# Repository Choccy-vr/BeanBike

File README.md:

# BeanBike

A DIY smart eBike display and controller.

## Why?

I made this because I really like eBikes; they are just fun. I have always wanted my own, but off the shelf they are way too expensive. So I thought of going the custom route, making my own controller. But then I thought, if I am really going to do this, I am not going to get some normal boring eBike I want my eBike. And that is how this came to be.

## Pictures!

### PCBs

#### Controller

#### Display

## BOM

|Product Name           |Product Description            |Product Link                                                                                                                                                                                                                                                                                                                                                                                                                                                                                                                                                                                                                                                                                                                                                                        |Product unit price|Product amount|Product Cost|Total (Before Tax + Shipping)|Total (Without Shipping)|Total  |
|-----------------------|-------------------------------|------------------------------------------------------------------------------------------------------------------------------------------------------------------------------------------------------------------------------------------------------------------------------------------------------------------------------------------------------------------------------------------------------------------------------------------------------------------------------------------------------------------------------------------------------------------------------------------------------------------------------------------------------------------------------------------------------------------------------------------------------------------------------------|------------------|--------------|------------|-----------------------------|------------------------|-------|
|Display-PCB            |PCB for display                |https://jlcpcb.com/                                                                                                                                                                                                                                                                                                                                                                                                                                                                                                                                                                                                                                                                                                                                                                 |4.12              |5             |$20.58      |$198.40                      |$212.29                 |$259.05|
|2x20 Socket            |Socket for Pi                  |https://www.digikey.com/en/products/detail/sullins-connector-solutions/SFH11-PBPC-D20-ST-BK/1990093                                                                                                                                                                                                                                                                                                                                                                                                                                                                                                                                                                                                                                                                                 |1.52              |1             |$1.52       |                             |                        |       |
|2x3 Header             |Expansion Pins                 |https://www.digikey.com/en/products/detail/sullins-connector-solutions/PBC03DAAN/861061                                                                                                                                                                                                                                                                                                                                                                                                                                                                                                                                                                                                                                                                                             |0.58              |2             |$1.16       |                             |                        |       |
|Display                |Display for eBike              |https://www.waveshare.com/product/displays/lcd-oled/lcd-oled-2/3.5inch-480x800-lcd.htm                                                                                                                                                                                                                                                                                                                                                                                                                                                                                                                                                                                                                                                                                              |44.99             |1             |$44.99      |                             |                        |       |
|Mini-HDMI to HDMI Cable|HDMI cable for display         |https://www.aliexpress.us/item/3256809615077123.html?spm=a2g0o.productlist.main.8.2665zmZAzmZA7N&aem_p4p_detail=202510251350533820414637980920002448901&algo_pvid=f852252a-7ad9-43c3-a8da-4e5a7b5fc53c&algo_exp_id=f852252a-7ad9-43c3-a8da-4e5a7b5fc53c-7&pdp_ext_f=%7B%22order%22%3A%22111%22%2C%22eval%22%3A%221%22%2C%22fromPage%22%3A%22search%22%7D&pdp_npi=6%40dis%21USD%214.00%210.99%21%21%214.00%210.99%21%402101d93a17614254531974823e32a0%2112000050211110398%21sea%21US%210%21ABX%211%210%21n_tag%3A-29910%3Bd%3A487c6e50%3Bm03_new_user%3A-29895%3BpisId%3A5000000187467530&curPageLogUid=s5fbXvPEQDyt&utparam-url=scene%3Asearch%7Cquery_from%3A%7Cx_object_id%3A1005009801391875%7C_p_origin_prod%3A&search_p4p_id=202510251350533820414637980920002448901_2         |1.99              |1             |$1.99       |                             |                        |       |
|Micro USB to USB C     |USB cable for display          |https://www.amazon.com/DteeDck-Adapter-Braided-Charging-Transmission/dp/B0BD36TZBK/ref=sr_1_3?crid=3JB4171DXJQSD&dib=eyJ2IjoiMSJ9.j7D2vrgbiLxGiZ8eLgHnYMRQBpcQriEWovB6tCvtnKIOLTDMlLoOxuHSk4-lcGFi6FHM3sO5ZKa8Dpr5FOVERj-xgS1iz99JzQZQLKl-xBtss3sl2CHqI4YVyfzRtf2d5FVlPNSBYPWBQrEoF8NK4ZHuYwldOKcTSCQnjOlM151Fnkp-68gktMK4j8L4pV9yZ8vR2BQQJ_acJUp5917qMGRKSj0DZvHJIeHgQgOO5zU.jbqUbGmHJq4WOtimEhEP5bUgwDAqksgkR2hxvEs_soo&dib_tag=se&keywords=micro%2Busb%2Bto%2Busb%2Bc&qid=1761426126&sprefix=micro%2Busb%2Bto%2Busb%2Caps%2C197&sr=8-3&th=1                                                                                                                                                                                                                                      |5.49              |1             |$5.49       |                             |                        |       |
|Controller-PCB         |PCB for controller             |https://jlcpcb.com/                                                                                                                                                                                                                                                                                                                                                                                                                                                                                                                                                                                                                                                                                                                                                                 |11.77             |5             |$58.87      |                             |                        |       |
|                       |                               |                                                                                                                                                                                                                                                                                                                                                                                                                                                                                                                                                                                                                                                                                                                                                                                    |                  |              |            |                             |                        |       |
|CSS2H-2512R-1L00F      |Shunt Resistors                |https://www.digikey.com/en/products/detail/bourns-inc/CSS2H-2512R-1L00F/6023764                                                                                                                                                                                                                                                                                                                                                                                                                                                                                                                                                                                                                                                                                                     |1.27              |3             |$3.81       |                             |                        |       |
|                       |                               |                                                                                                                                                                                                                                                                                                                                                                                                                                                                                                                                                                                                                                                                                                                                                                                    |                  |              |            |                             |                        |       |
|PAS sensor             |Pas Sensor                     |https://www.aliexpress.us/item/3256808182150916.html?spm=a2g0o.cart.0.0.15007a9db9tmpl&mp=1&pdp_npi=5%40dis%21USD%21USD%204.99%21USD%201.99%21%21USD%201.99%21%21%21%402103128817614453809426246ef042%2112000044743553170%21ct%21US%213108417632%21%211%210&_gl=1*1ddvozz*_gcl_au*MTU0MTkyODcyNS4xNzYwMTQ1Mzcx*_ga*MjA2ODc0MDM2Ni4xNzYxNDQ1Mzgy*_ga_VED1YSGNC7*czE3NjE0NDUzODIkbzEkZzAkdDE3NjE0NDUzODIkajYwJGwwJGgw&gatewayAdapt=glo2usa                                                                                                                                                                                                                                                                                                                                            |1.99              |1             |$1.99       |                             |                        |       |
|Throttle sensor        |Twist Throttle Handle          |https://www.aliexpress.us/item/3256806514034716.html?spm=a2g0o.cart.0.0.c69c38da9vOmau&mp=1&pdp_npi=5%40dis%21USD%21USD%204.63%21USD%201.99%21%21USD%201.99%21%21%21%40210337c117627140379221353e809b%2112000038044279289%21ct%21US%213108417632%21%211%210&_gl=1*1l540z1*_gcl_au*MTU0MTkyODcyNS4xNzYwMTQ1Mzcx*_ga*MjA2ODc0MDM2Ni4xNzYxNDQ1Mzgy*_ga_VED1YSGNC7*czE3NjI3MTQwMzEkbzMkZzEkdDE3NjI3MTQwMzkkajUyJGwwJGgw&gatewayAdapt=glo2usa                                                                                                                                                                                                                                                                                                                                            |1.99              |1             |$1.99       |                             |                        |       |
|Brake sensor           |Brake/shut off sensor          |https://www.aliexpress.us/item/3256805985764030.html?spm=a2g0o.cart.0.0.c69c38da9vOmau&mp=1&pdp_npi=5%40dis%21USD%21USD%2011.66%21USD%202.90%21%21USD%202.90%21%21%21%40210337c117627140379221353e809b%2112000036110573258%21ct%21US%213108417632%21%211%210&_gl=1*1sw3duy*_gcl_au*MTU0MTkyODcyNS4xNzYwMTQ1Mzcx*_ga*MjA2ODc0MDM2Ni4xNzYxNDQ1Mzgy*_ga_VED1YSGNC7*czE3NjI3MTQwMzEkbzMkZzEkdDE3NjI3MTQwNDgkajQzJGwwJGgw&gatewayAdapt=glo2usa                                                                                                                                                                                                                                                                                                                                           |5.9               |1             |$5.90       |                             |                        |       |
|MOSFET Heatsinks       |Heatsink for MOSFETs           |https://www.aliexpress.us/item/3256803892794950.html?spm=a2g0o.productlist.main.1.13c62810kwHGNA&algo_pvid=aa161256-cc13-4f43-9ac4-79cdfe83af14&algo_exp_id=aa161256-cc13-4f43-9ac4-79cdfe83af14-0&pdp_ext_f=%7B%22order%22%3A%222400%22%2C%22eval%22%3A%221%22%2C%22fromPage%22%3A%22search%22%7D&pdp_npi=6%40dis%21USD%212.12%211.99%21%21%2115.01%2114.09%21%402101d83f17614455184686341ee64b%2112000030401636260%21sea%21US%213108417632%21X%211%210%21n_tag%3A-29919%3Bd%3A487c6e50%3Bm03_new_user%3A-29895%3BpisId%3A5000000190801969&curPageLogUid=eevL79xpdQiV&utparam-url=scene%3Asearch%7Cquery_from%3A%7Cx_object_id%3A1005004079109702%7C_p_origin_prod%3A                                                                                                              |0.2               |10            |$1.99       |                             |                        |       |
|M8 Connector 2P        |Connector for brake sensor     |https://www.aliexpress.us/item/3256805115817349.html?spm=a2g0o.cart.0.0.765938daCeJANz&mp=1&pdp_npi=5%40dis%21USD%21USD%202.97%21USD%202.97%21%21USD%202.94%21%21%21%402101f11417614462386586215ea526%2112000032551815683%21ct%21US%213108417632%21%211%210&_gl=1*j0wktf*_gcl_au*MTU0MTkyODcyNS4xNzYwMTQ1Mzcx*_ga*MjA2ODc0MDM2Ni4xNzYxNDQ1Mzgy*_ga_VED1YSGNC7*czE3NjE0NDUzODIkbzEkZzEkdDE3NjE0NDYyNDAkajMkbDAkaDA.&gatewayAdapt=glo2usa                                                                                                                                                                                                                                                                                                                                             |2.97              |1             |$2.97       |                             |                        |       |
|M8 Connectors 3P       |Connectors for PAS and Throttle|https://www.aliexpress.us/item/3256805115817349.html?spm=a2g0o.cart.0.0.765938daCeJANz&mp=1&pdp_npi=5%40dis%21USD%21USD%206.99%21USD%206.99%21%21USD%206.92%21%21%21%402101f11417614462386586215ea526%2112000032551815696%21ct%21US%213108417632%21%211%210&_gl=1*j0wktf*_gcl_au*MTU0MTkyODcyNS4xNzYwMTQ1Mzcx*_ga*MjA2ODc0MDM2Ni4xNzYxNDQ1Mzgy*_ga_VED1YSGNC7*czE3NjE0NDUzODIkbzEkZzEkdDE3NjE0NDYyNDAkajMkbDAkaDA.&gatewayAdapt=glo2usa                                                                                                                                                                                                                                                                                                                                             |1.75              |4             |$6.99       |                             |                        |       |
|M8 Connector 6P        |Connector for Display          |https://www.aliexpress.us/item/3256805115817349.html?spm=a2g0o.cart.0.0.765938daCeJANz&mp=1&pdp_npi=5%40dis%21USD%21USD%203.46%21USD%203.46%21%21USD%203.43%21%21%21%402101f11417614462386586215ea526%2112000038599641962%21ct%21US%213108417632%21%211%210&_gl=1*1hyuy1y*_gcl_au*MTU0MTkyODcyNS4xNzYwMTQ1Mzcx*_ga*MjA2ODc0MDM2Ni4xNzYxNDQ1Mzgy*_ga_VED1YSGNC7*czE3NjE0NDUzODIkbzEkZzEkdDE3NjE0NDYyNDMkajYwJGwwJGgw&gatewayAdapt=glo2usa                                                                                                                                                                                                                                                                                                                                            |3.46              |1             |$2.97       |                             |                        |       |
|MOSFETs                |MOSFETs                        |https://www.digikey.com/en/products/detail/infineon-technologies/IRFB4110PBFXKMA1/22157630                                                                                                                                                                                                                                                                                                                                                                                                                                                                                                                                                                                                                                                                                          |3.06              |6             |$18.36      |                             |                        |       |
|Capacitor 680uF        |big cap for controller         |https://www.digikey.com/en/products/detail/chemi-con/EKZN630ELL681MK30S/4843904                                                                                                                                                                                                                                                                                                                                                                                                                                                                                                                                                                                                                                                                                                     |1.53              |1             |$1.53       |                             |                        |       |
|Capacitor 330uF        |big cap for controller         |https://www.digikey.com/en/products/detail/rubycon/25ZLJ330M8X11-5/3134207                                                                                                                                                                                                                                                                                                                                                                                                                                                                                                                                                                                                                                                                                                          |0.54              |1             |$0.54       |                             |                        |       |
|Screw Terminal         |Phase Connector                |https://www.digikey.com/en/products/detail/keystone-electronics/8196/316832                                                                                                                                                                                                                                                                                                                                                                                                                                                                                                                                                                                                                                                                                                         |1.24              |3             |$3.72       |                             |                        |       |
|Ring Connector         |Phase Wire connector           |https://www.digikey.com/en/products/detail/molex/0191930245/1952714                                                                                                                                                                                                                                                                                                                                                                                                                                                                                                                                                                                                                                                                                                                 |0.53              |3             |$1.59       |                             |                        |       |
|GPS module             |GPS module                     |https://www.aliexpress.us/item/3256806636967867.html?spm=a2g0o.productlist.main.8.5f294519Xppi6X&aem_p4p_detail=202511091049282176669761148710002202146&algo_pvid=408d6edc-35f6-4694-a5b1-e4b75c03ea1d&algo_exp_id=408d6edc-35f6-4694-a5b1-e4b75c03ea1d-7&pdp_ext_f=%7B%22order%22%3A%22161%22%2C%22eval%22%3A%221%22%2C%22fromPage%22%3A%22search%22%7D&pdp_npi=6%40dis%21USD%215.18%212.18%21%21%2136.69%2115.43%21%402101dedf17627141680806432e8079%2112000038417528859%21sea%21US%213108417632%21X%211%210%21n_tag%3A-29919%3Bd%3A487c6e50%3Bm03_new_user%3A-29895%3BpisId%3A5000000191724427&curPageLogUid=PXVcwqFInPA3&utparam-url=scene%3Asearch%7Cquery_from%3A%7Cx_object_id%3A1005006823282619%7C_p_origin_prod%3A&search_p4p_id=202511091049282176669761148710002202146_2|6.39              |1             |$6.39       |                             |                        |       |
|M8 Connector 5P        |Connector for ENCODER          |https://www.aliexpress.us/item/3256805115817349.html?spm=a2g0o.cart.0.0.765938daCeJANz&mp=1&pdp_npi=5%40dis%21USD%21USD%203.46%21USD%203.46%21%21USD%203.43%21%21%21%402101f11417614462386586215ea526%2112000038599641962%21ct%21US%213108417632%21%211%210&_gl=1*1hyuy1y*_gcl_au*MTU0MTkyODcyNS4xNzYwMTQ1Mzcx*_ga*MjA2ODc0MDM2Ni4xNzYxNDQ1Mzgy*_ga_VED1YSGNC7*czE3NjE0NDUzODIkbzEkZzEkdDE3NjE0NDYyNDMkajYwJGwwJGgw&gatewayAdapt=glo2usa                                                                                                                                                                                                                                                                                                                                            |3.06              |1             |$3.06       |                             |                        |       |

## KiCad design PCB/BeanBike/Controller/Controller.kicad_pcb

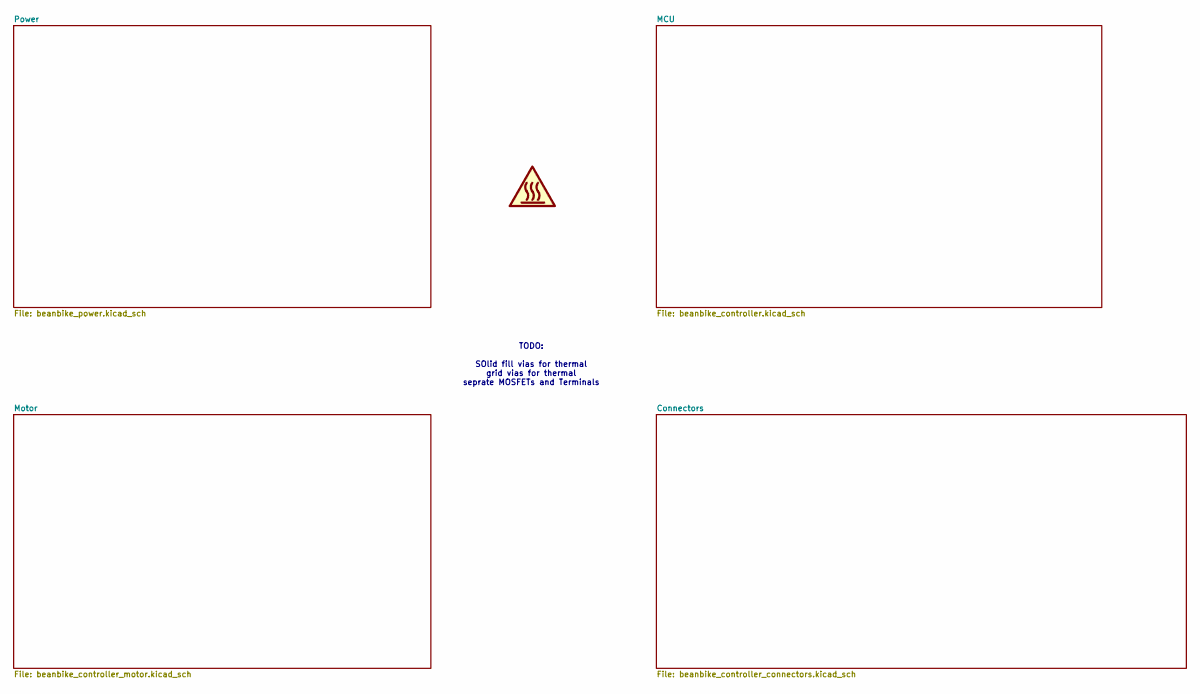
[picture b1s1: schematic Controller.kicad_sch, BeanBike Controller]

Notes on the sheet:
TODO: SOlid fill vias for thermal grid vias for thermal seprate MOSFETs and Terminals

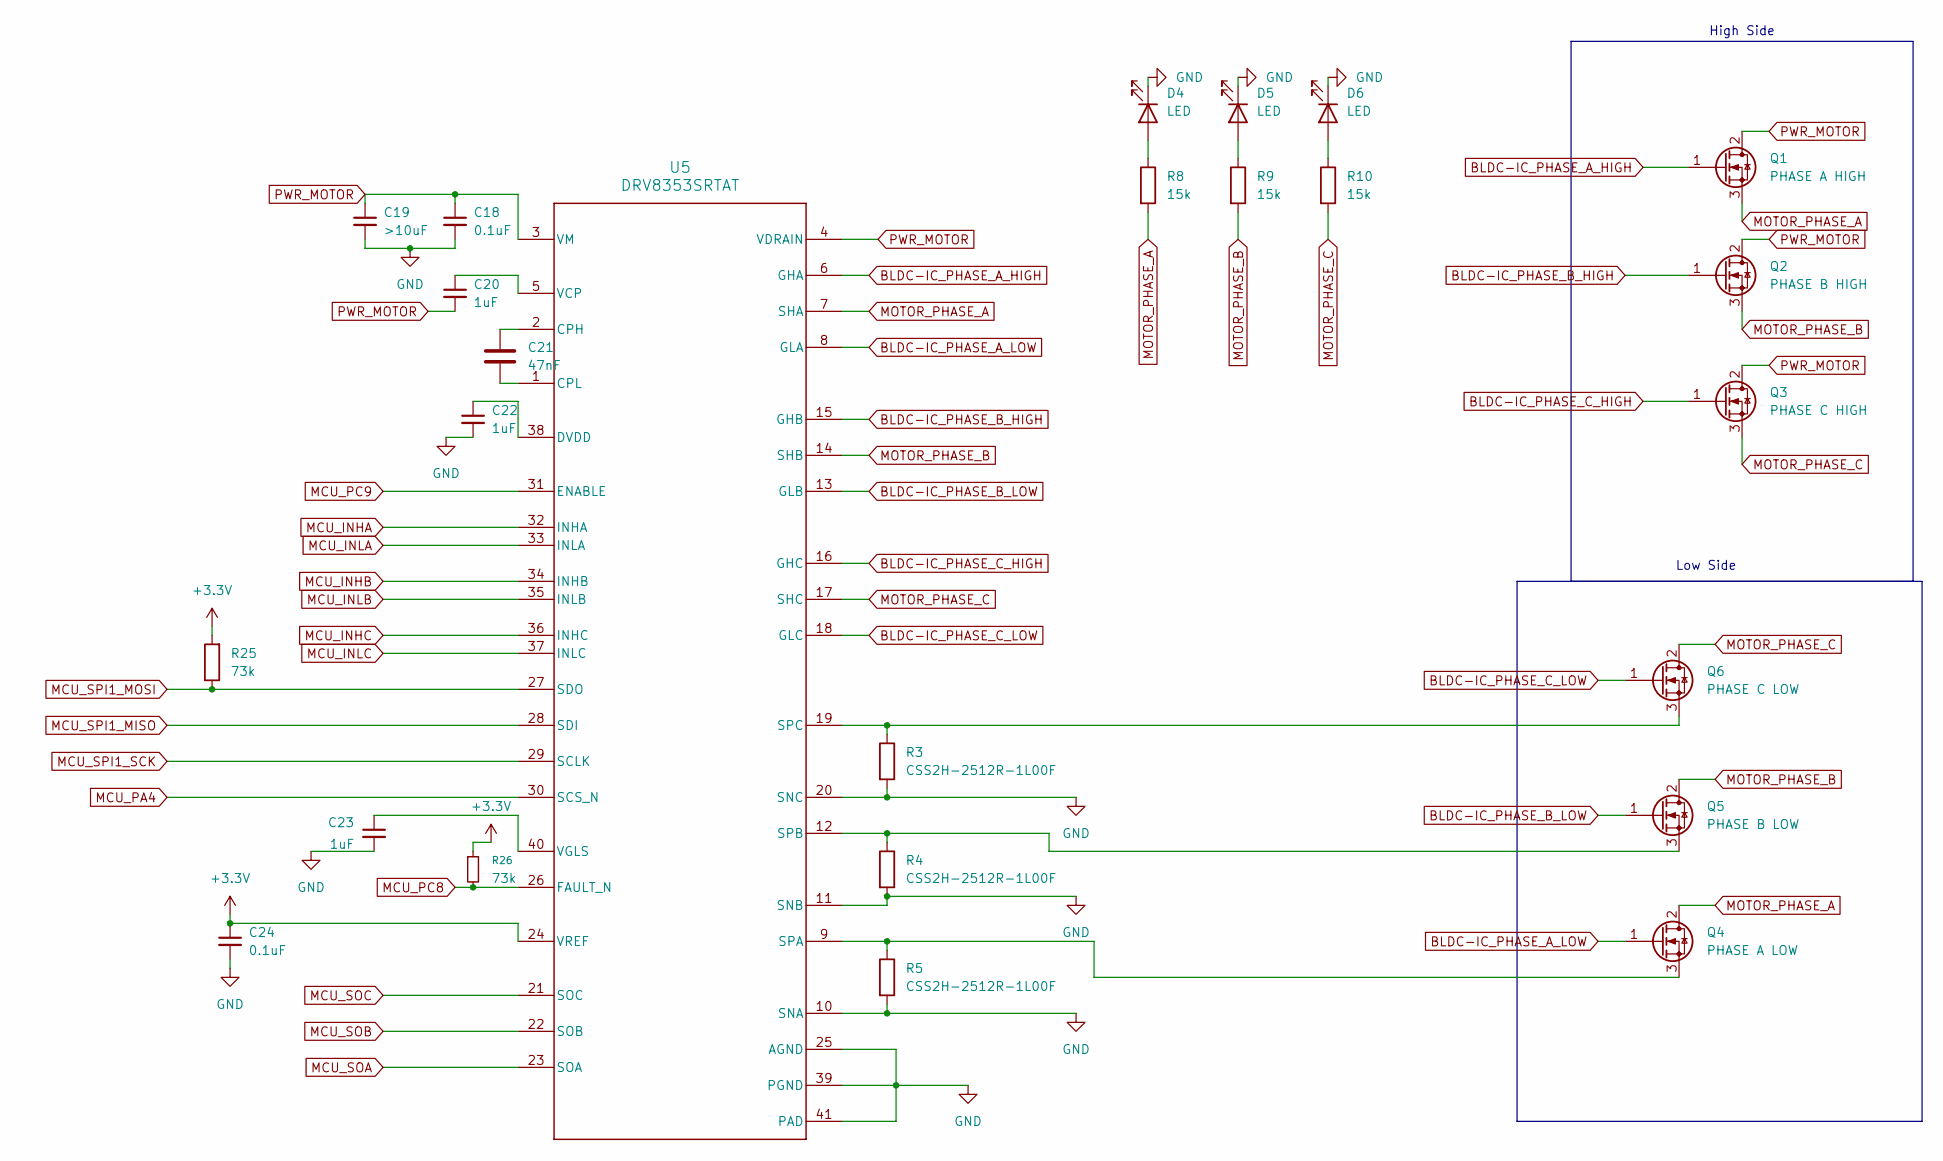
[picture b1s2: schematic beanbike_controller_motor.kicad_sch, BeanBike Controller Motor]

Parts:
C18, C24: 0.1uF; C_0402_1005Metric; LCSC C1525
C19: >10uF; C_0805_2012Metric; LCSC C45783
C20, C22, C23: 1uF; C_0402_1005Metric; LCSC C52923
C21: 47nF; C_0603_1608Metric; LCSC C1622
D4, D5, D6: LED; LED_0603_1608Metric; LCSC C2286
Q1: PHASE A HIGH; TO254P1050X476X2020-3
Q2: PHASE B HIGH; TO254P1050X476X2020-3
Q3: PHASE C HIGH; TO254P1050X476X2020-3
Q4: PHASE A LOW; TO254P1050X476X2020-3
Q5: PHASE B LOW; TO254P1050X476X2020-3
Q6: PHASE C LOW; TO254P1050X476X2020-3
R3, R4, R5: CSS2H-2512R-1L00F; RES_1L00x_BRN; LCSC C4175647
R8, R9, R10: 15k; R_0805_2012Metric; LCSC C17475
R25, R26: 73k; R_0805_2012Metric; LCSC C17819
U5: DRV8353SRTAT; QFN50P600X600X80-41N; LCSC C2150480

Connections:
+3.3V: C24.1, R25.2, R26.1, U5.24 (VREF); also elsewhere on the board
BLDC-IC_PHASE_A_HIGH: Q1.1 (G), U5.6 (GHA)
BLDC-IC_PHASE_A_LOW: Q4.1 (G), U5.8 (GLA)
BLDC-IC_PHASE_B_HIGH: Q2.1 (G), U5.15 (GHB)
BLDC-IC_PHASE_B_LOW: Q5.1 (G), U5.13 (GLB)
BLDC-IC_PHASE_C_HIGH: Q3.1 (G), U5.16 (GHC)
BLDC-IC_PHASE_C_LOW: Q6.1 (G), U5.18 (GLC)
BRAKE_GND: C18.2, C19.2, C22.2, C23.2, C24.2, D4.1 (K), D5.1 (K), D6.1 (K), R3.2, R4.2, R5.2, U5.10 (SNA), U5.11 (SNB), U5.20 (SNC), U5.25 (AGND), U5.39 (PGND), U5.41 (PAD); also elsewhere on the board
MCU_INHA: U5.32 (INHA); also elsewhere on the board
MCU_INHB: U5.34 (INHB); also elsewhere on the board
MCU_INHC: U5.36 (INHC); also elsewhere on the board
MCU_INLA: U5.33 (INLA); also elsewhere on the board
MCU_INLB: U5.35 (INLB); also elsewhere on the board
MCU_INLC: U5.37 (INLC); also elsewhere on the board
MCU_PA4: U5.30 (SCS_N); also elsewhere on the board
MCU_PC8: R26.2, U5.26 (FAULT_N); also elsewhere on the board
MCU_PC9: U5.31 (ENABLE); also elsewhere on the board
MCU_SOA: U5.23 (SOA); also elsewhere on the board
MCU_SOB: U5.22 (SOB); also elsewhere on the board
MCU_SOC: U5.21 (SOC); also elsewhere on the board
MCU_SPI1_MISO: U5.28 (SDI); also elsewhere on the board
MCU_SPI1_MOSI: R25.1, U5.27 (SDO); also elsewhere on the board
MCU_SPI1_SCK: U5.29 (SCLK); also elsewhere on the board
MOTOR_PHASE_A: Q1.3 (S), Q4.2 (D), R8.2, U5.7 (SHA); also elsewhere on the board
MOTOR_PHASE_B: Q2.3 (S), Q5.2 (D), R9.2, U5.14 (SHB); also elsewhere on the board
MOTOR_PHASE_C: Q3.3 (S), Q6.2 (D), R10.2, U5.17 (SHC); also elsewhere on the board
unnamed: D4.2 (A), R8.1
unnamed: D5.2 (A), R9.1
unnamed: D6.2 (A), R10.1
unnamed: Q4.3 (S), R5.1, U5.9 (SPA)
unnamed: Q5.3 (S), R4.1, U5.12 (SPB)
unnamed: Q6.3 (S), R3.1, U5.19 (SPC)
unnamed: C21.1, U5.2 (CPH)
unnamed: C21.2, U5.1 (CPL)
unnamed: C22.1, U5.38 (DVDD)
unnamed: C20.1, U5.5 (VCP)
unnamed: C23.1, U5.40 (VGLS)
PWR_MOTOR: C18.1, C19.1, C20.2, Q1.2 (D), Q2.2 (D), Q3.2 (D), U5.3 (VM), U5.4 (VDRAIN); also elsewhere on the board

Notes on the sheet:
High Side
Low Side

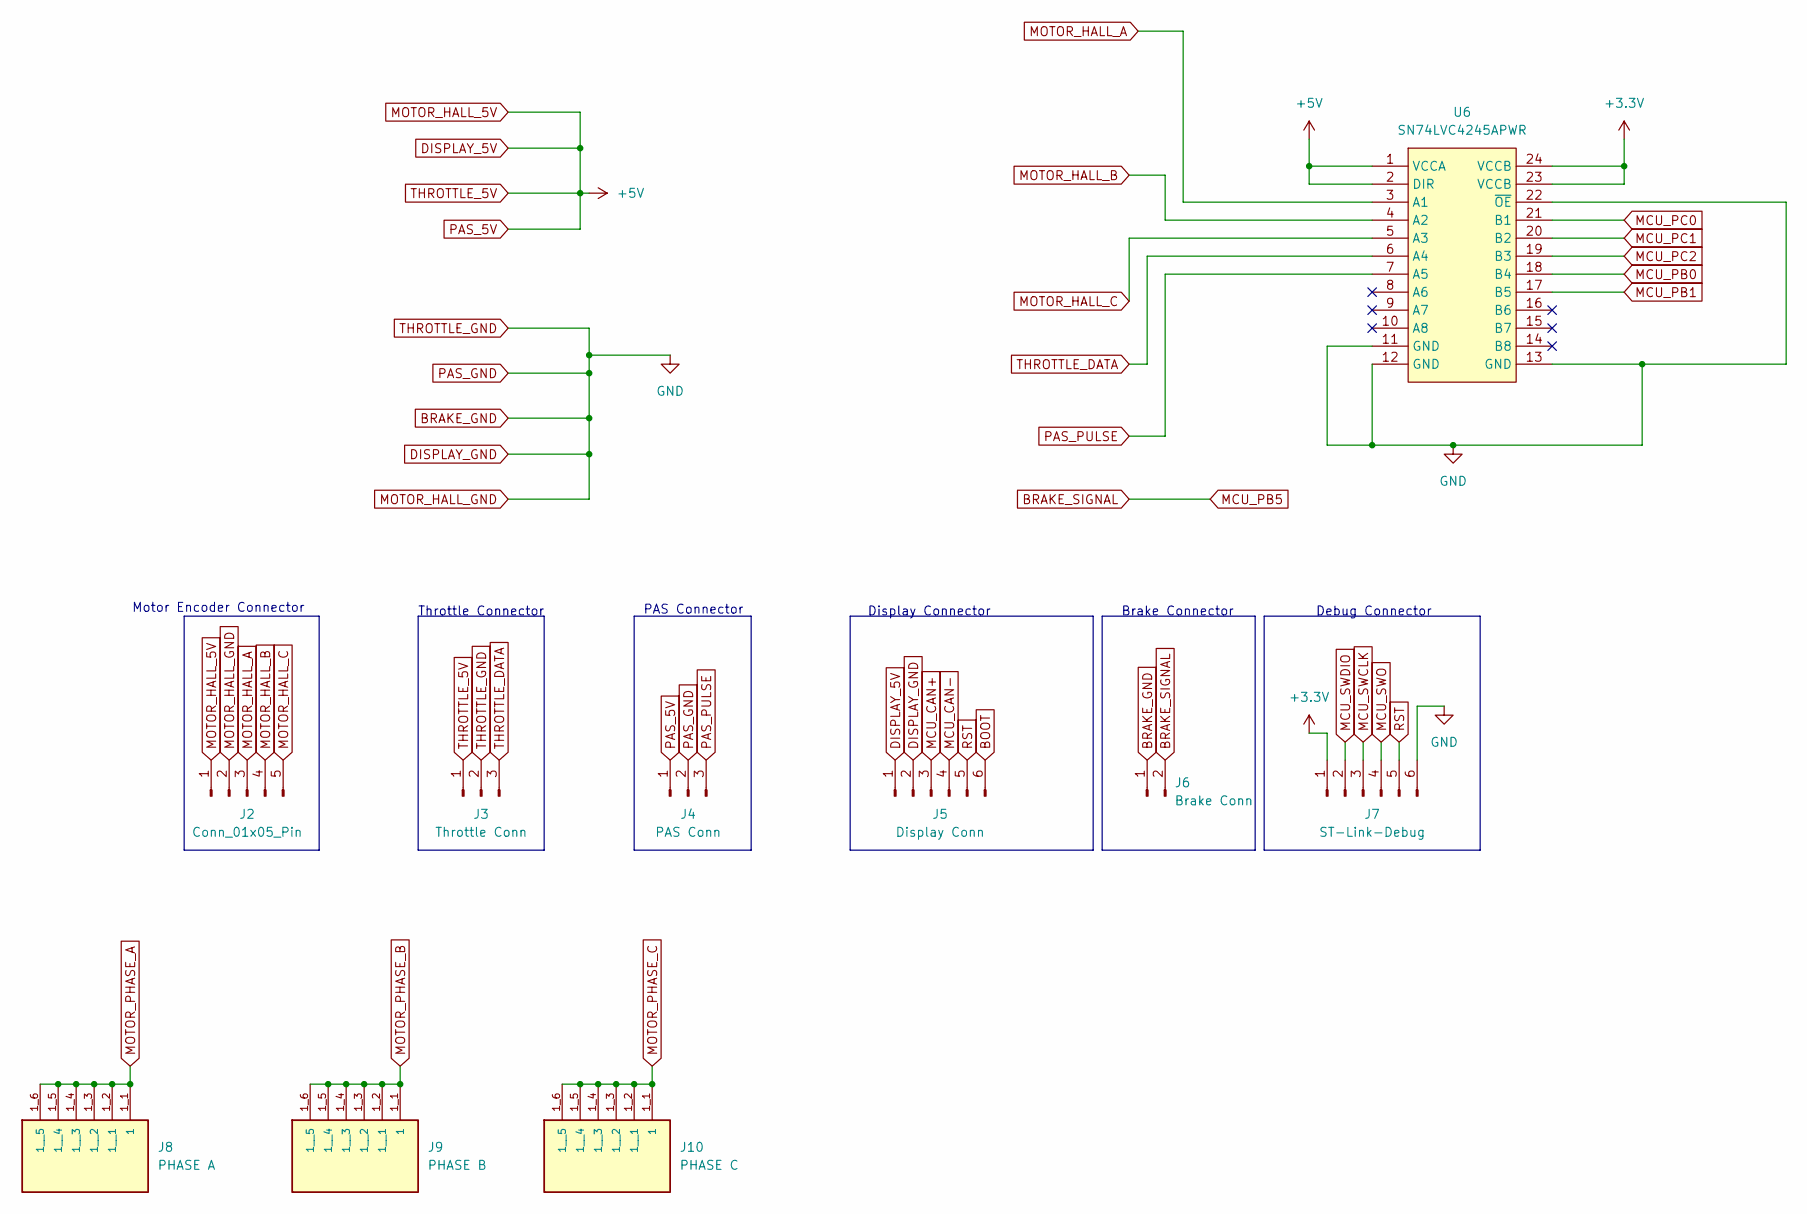
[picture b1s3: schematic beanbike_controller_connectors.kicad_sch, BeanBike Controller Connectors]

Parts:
J2: Conn_01x05_Pin; PinHeader_1x05_P2.54mm_Vertical
J3: Throttle Conn; PinHeader_1x03_P2.54mm_Vertical
J4: PAS Conn; PinHeader_1x03_P2.54mm_Vertical
J5: Display Conn; PinHeader_1x06_P2.54mm_Vertical
J6: Brake Conn; PinHeader_1x02_P2.54mm_Vertical
J7: ST-Link-Debug; PinHeader_1x06_P2.54mm_Vertical
J8: PHASE A; KEYSTONE_8196; PARTREV D
J9: PHASE B; KEYSTONE_8196; PARTREV D
J10: PHASE C; KEYSTONE_8196; PARTREV D
U6: SN74LVC4245APWR; TSSOP-24_L7.8-W4.4-P0.65-LS6.4-BL; LCSC Part C7859

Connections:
+3.3V: J7.1, U6.23 (VCCB), U6.24 (VCCB); also elsewhere on the board
BOOT: J5.6; also elsewhere on the board
BRAKE_GND: J2.2, J3.2, J4.2, J5.2, J6.1, J7.6, U6.11 (GND), U6.12 (GND), U6.13 (GND), U6.22 (~OE); also elsewhere on the board
BRAKE_SIGNAL: J6.2; also elsewhere on the board
DISPLAY_5V: J2.1, J3.1, J4.1, J5.1, U6.1 (VCCA), U6.2 (DIR); also elsewhere on the board
MCU_CAN+: J5.3; also elsewhere on the board
MCU_CAN-: J5.4; also elsewhere on the board
MCU_PB0: U6.18 (B4); also elsewhere on the board
MCU_PB1: U6.17 (B5); also elsewhere on the board
MCU_PC0: U6.21 (B1); also elsewhere on the board
MCU_PC1: U6.20 (B2); also elsewhere on the board
MCU_PC2: U6.19 (B3); also elsewhere on the board
MCU_SWCLK: J7.3; also elsewhere on the board
MCU_SWDIO: J7.2; also elsewhere on the board
MCU_SWO: J7.4; also elsewhere on the board
MOTOR_HALL_A: J2.3, U6.3 (A1)
MOTOR_HALL_B: J2.4, U6.4 (A2)
MOTOR_HALL_C: J2.5, U6.5 (A3)
MOTOR_PHASE_A: J8.1_1 (1), J8.1_2 (1__1), J8.1_3 (1__2), J8.1_4 (1__3), J8.1_5 (1__4), J8.1_6 (1__5); also elsewhere on the board
MOTOR_PHASE_B: J9.1_1 (1), J9.1_2 (1__1), J9.1_3 (1__2), J9.1_4 (1__3), J9.1_5 (1__4), J9.1_6 (1__5); also elsewhere on the board
MOTOR_PHASE_C: J10.1_1 (1), J10.1_2 (1__1), J10.1_3 (1__2), J10.1_4 (1__3), J10.1_5 (1__4), J10.1_6 (1__5); also elsewhere on the board
PAS_PULSE: J4.3, U6.7 (A5)
RST: J5.5, J7.5; also elsewhere on the board
THROTTLE_DATA: J3.3, U6.6 (A4)

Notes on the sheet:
Debug Connector
Display Connector
Throttle Connector
PAS Connector
Brake Connector
Motor Encoder Connector

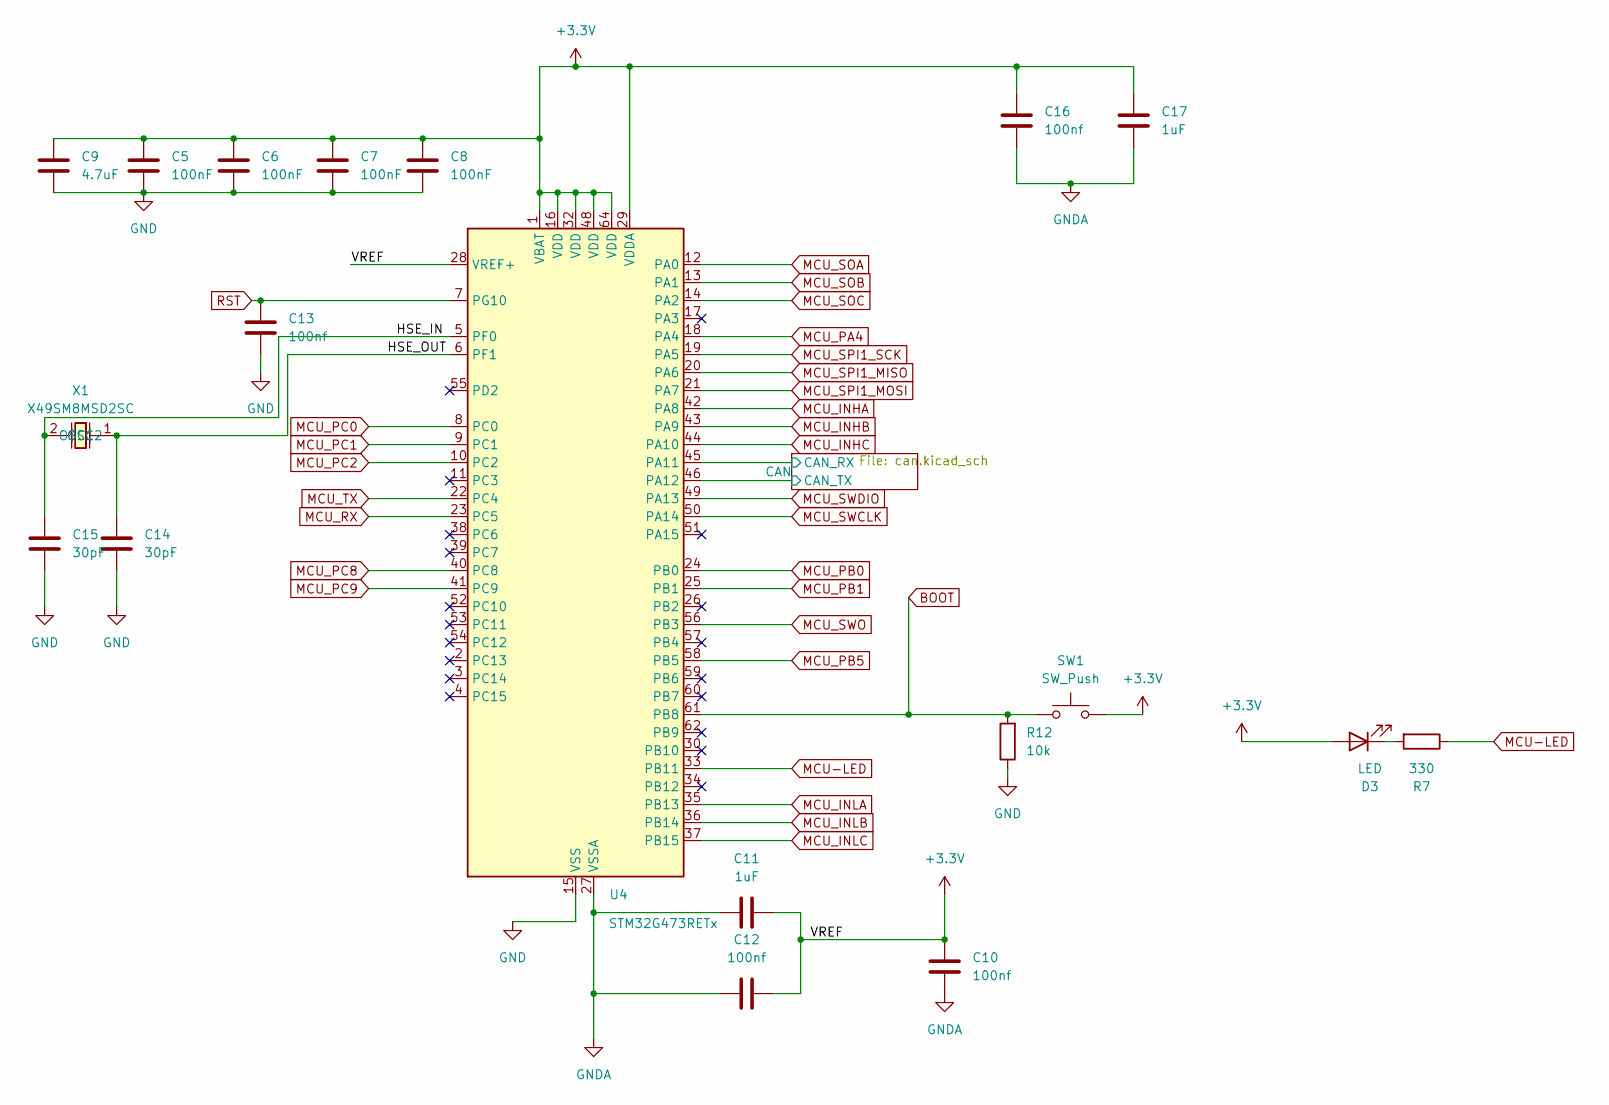
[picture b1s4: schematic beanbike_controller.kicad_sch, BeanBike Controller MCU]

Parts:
C5, C6, C7, C8: 100nF; C_0402_1005Metric; LCSC C1525
C9: 4.7uF; C_0402_1005Metric; LCSC C1569
C10, C12, C13, C16: 100nf; C_0402_1005Metric; LCSC C1525
C11, C17: 1uF; C_0402_1005Metric; LCSC C52923
C14, C15: 30pF; C_0402_1005Metric; LCSC C1570
D3: LED; LED_0805_2012Metric; LCSC C2297
R7: 330; R_0805_2012Metric; LCSC C17630
R12: 10k; R_0805_2012Metric; LCSC C17414
SW1: SW_Push; SW-SMD_L3.9-W3.0-P4.45; LCSC C720477
U4: STM32G473RETx; LQFP-64_10x10mm_P0.5mm; LCSC C730120
X1: X49SM8MSD2SC; CRYSTAL-SMD_L11.5-W4.8-LS12.7; LCSC Part C12674

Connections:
+3.3V: C5.2, C6.2, C7.2, C8.2, C9.1, C10.1, C11.2, C12.2, C16.1, C17.1, D3.2 (A), SW1.2, U4.1 (VBAT), U4.16 (VDD), U4.28 (VREF+), U4.29 (VDDA), U4.32 (VDD), U4.48 (VDD), U4.64 (VDD); also elsewhere on the board
/MCU/CAN/CAN_RX: U4.45 (PA11); also elsewhere on the board
/MCU/CAN/CAN_TX: U4.46 (PA12); also elsewhere on the board
/MCU/HSE_IN: C15.1, U4.5 (PF0), X1.2 (OSC2)
/MCU/HSE_OUT: C14.1, U4.6 (PF1), X1.1 (OSC1)
BOOT: R12.2, SW1.1, U4.61 (PB8); also elsewhere on the board
BRAKE_GND: C5.1, C6.1, C7.1, C8.1, C9.2, C13.2, C14.2, C15.2, R12.1, U4.15 (VSS), U4.31 (VSS), U4.47 (VSS), U4.63 (VSS); also elsewhere on the board
BRAKE_SIGNAL: U4.58 (PB5); also elsewhere on the board
GNDA: C10.2, C11.1, C12.1, C16.2, C17.2, U4.27 (VSSA)
MCU-LED: R7.1, U4.33 (PB11)
MCU_INHA: U4.42 (PA8); also elsewhere on the board
MCU_INHB: U4.43 (PA9); also elsewhere on the board
MCU_INHC: U4.44 (PA10); also elsewhere on the board
MCU_INLA: U4.35 (PB13); also elsewhere on the board
MCU_INLB: U4.36 (PB14); also elsewhere on the board
MCU_INLC: U4.37 (PB15); also elsewhere on the board
MCU_PA4: U4.18 (PA4); also elsewhere on the board
MCU_PB0: U4.24 (PB0); also elsewhere on the board
MCU_PB1: U4.25 (PB1); also elsewhere on the board
MCU_PC0: U4.8 (PC0); also elsewhere on the board
MCU_PC1: U4.9 (PC1); also elsewhere on the board
MCU_PC2: U4.10 (PC2); also elsewhere on the board
MCU_PC8: U4.40 (PC8); also elsewhere on the board
MCU_PC9: U4.41 (PC9); also elsewhere on the board
MCU_RX: U4.23 (PC5)
MCU_SOA: U4.12 (PA0); also elsewhere on the board
MCU_SOB: U4.13 (PA1); also elsewhere on the board
MCU_SOC: U4.14 (PA2); also elsewhere on the board
MCU_SPI1_MISO: U4.20 (PA6); also elsewhere on the board
MCU_SPI1_MOSI: U4.21 (PA7); also elsewhere on the board
MCU_SPI1_SCK: U4.19 (PA5); also elsewhere on the board
MCU_SWCLK: U4.50 (PA14); also elsewhere on the board
MCU_SWDIO: U4.49 (PA13); also elsewhere on the board
MCU_SWO: U4.56 (PB3); also elsewhere on the board
MCU_TX: U4.22 (PC4)
unnamed: D3.1 (K), R7.2
RST: C13.1, U4.7 (PG10); also elsewhere on the board

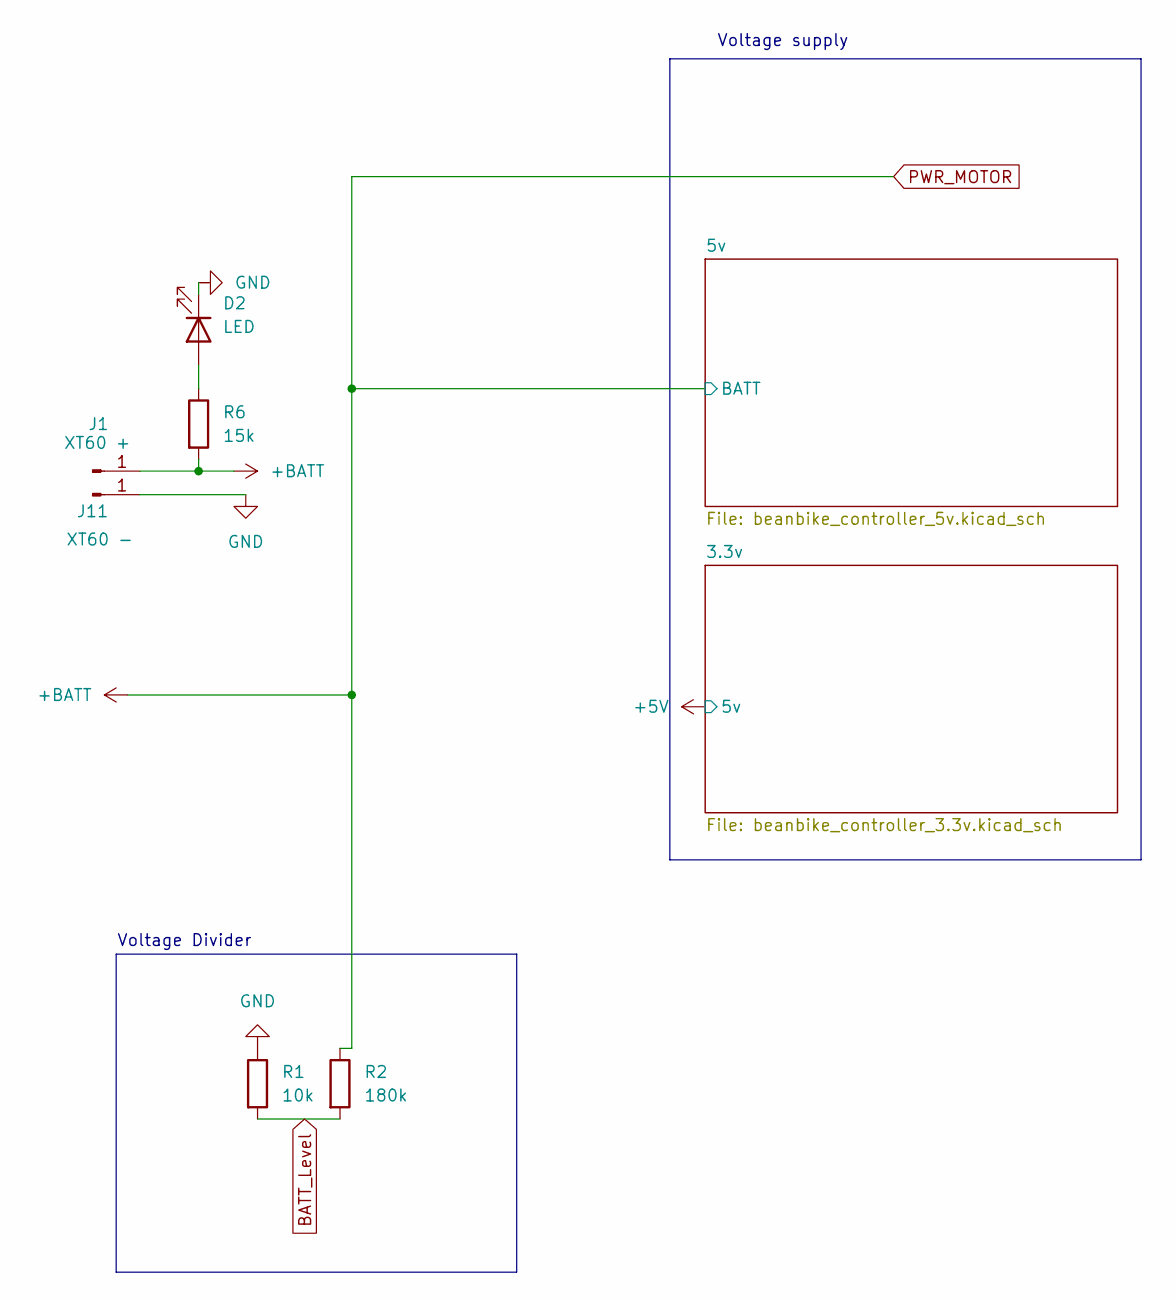
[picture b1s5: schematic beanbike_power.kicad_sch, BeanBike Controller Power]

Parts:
D2: LED; LED_0603_1608Metric; LCSC C2286
J1: XT60 +; MountingHole_3.2mm_M3_Pad_Via
J11: XT60 -; MountingHole_3.2mm_M3_Pad_Via
R1: 10k; R_0805_2012Metric; LCSC C17414
R2: 180k; R_0805_2012Metric; LCSC C17501
R6: 15k; R_0805_2012Metric; LCSC C17475

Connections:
BATT_Level: R1.2, R2.2
BRAKE_GND: D2.1 (K), J11.1, R1.1; also elsewhere on the board
unnamed: D2.2 (A), R6.1
PWR_MOTOR: J1.1, R2.1, R6.2; also elsewhere on the board

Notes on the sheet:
Voltage Divider
Voltage supply

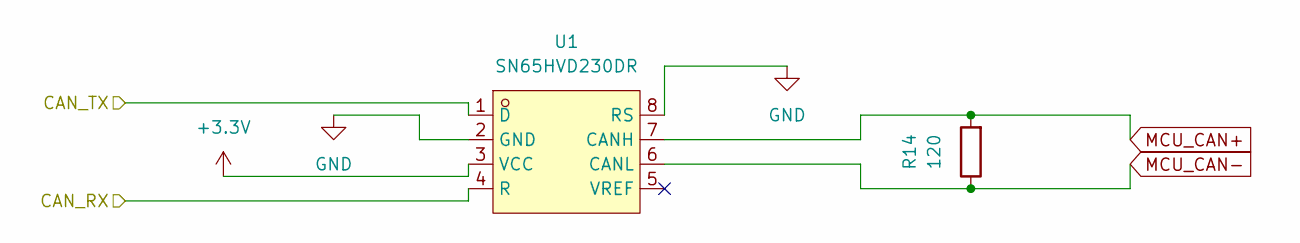
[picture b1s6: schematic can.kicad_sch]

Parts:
R14: 120; R_0805_2012Metric; LCSC C17437
U1: SN65HVD230DR; SOIC-8_L4.9-W3.9-P1.27-LS6.0-BL; LCSC Part C12084

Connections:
+3.3V: U1.3 (VCC); also elsewhere on the board
/MCU/CAN/CAN_RX: U1.4 (R); also elsewhere on the board
/MCU/CAN/CAN_TX: U1.1 (D); also elsewhere on the board
BRAKE_GND: U1.2 (GND), U1.8 (RS); also elsewhere on the board
MCU_CAN+: R14.2, U1.7 (CANH); also elsewhere on the board
MCU_CAN-: R14.1, U1.6 (CANL); also elsewhere on the board

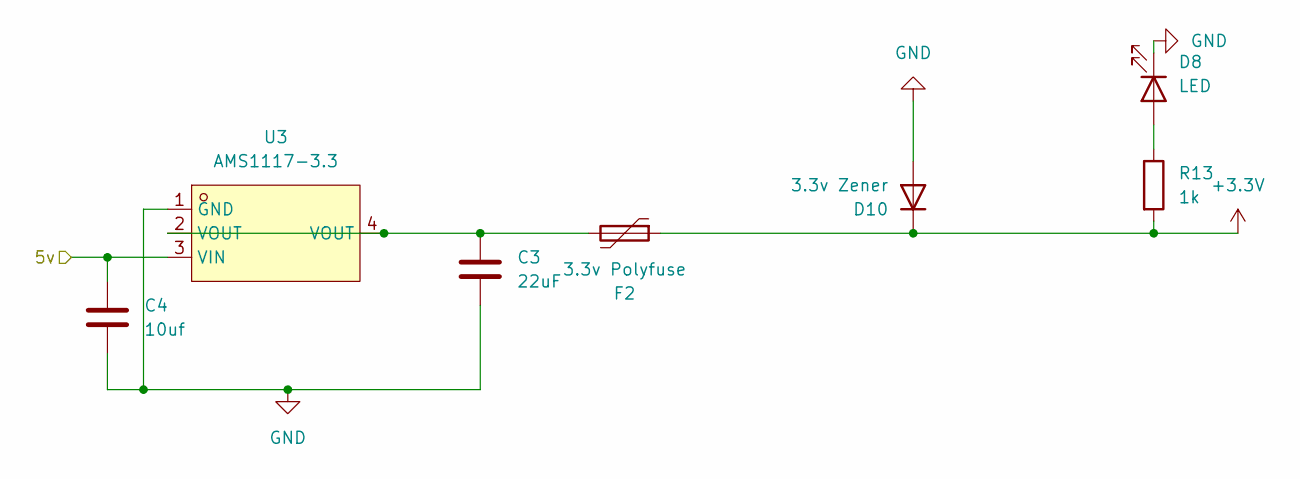
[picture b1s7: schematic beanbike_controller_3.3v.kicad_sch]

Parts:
C3: 22uF; C_0603_1608Metric; LCSC C59461
C4: 10uf; C_0402_1005Metric; LCSC C15525
D8: LED; LED_0603_1608Metric; LCSC C2290
D10: 3.3v Zener; D_SMA; LCSC C19077475
F2: 3.3v Polyfuse; FUSE_MF_R065_2_BRN
R13: 1k; R_0805_2012Metric; LCSC C17513
U3: AMS1117-3.3; SOT-223-3_L6.5-W3.4-P2.30-LS7.0-BR; LCSC Part C6186

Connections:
+3.3V: D10.1 (K), F2.1, R13.2; also elsewhere on the board
BRAKE_GND: C3.2, C4.2, D8.1 (K), D10.2 (A), U3.1 (GND); also elsewhere on the board
DISPLAY_5V: C4.1, U3.3 (VIN); also elsewhere on the board
unnamed: C3.1, F2.2, U3.2 (VOUT), U3.4 (VOUT)
unnamed: D8.2 (A), R13.1

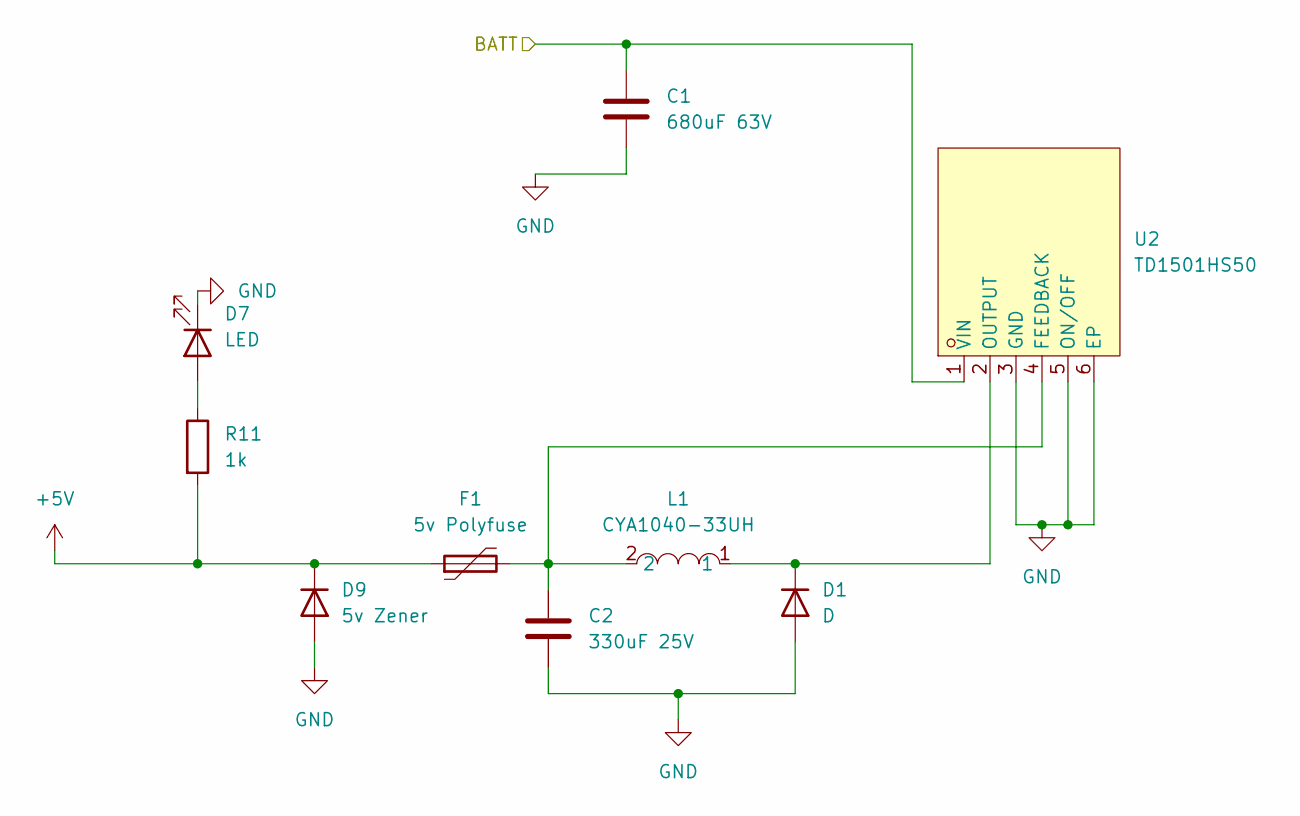
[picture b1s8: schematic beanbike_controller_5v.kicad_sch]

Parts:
C1: 680uF 63V; CP_Radial_D12.5mm_P5.00mm
C2: 330uF 25V; CP_Radial_D8.0mm_P3.50mm
D1: D; D_SOD-123F; LCSC C64898
D7: LED; LED_0603_1608Metric; LCSC C2296
D9: 5v Zener; D_SMA; LCSC C19077477
F1: 5v Polyfuse; FUS_RKEF300_TYCO_TYC
L1: CYA1040-33UH; IND-SMD_L11.6-W10.1; LCSC Part C6364680
R11: 1k; R_0805_2012Metric; LCSC C17513
U2: TD1501HS50; PG-TO-263-5_L10.2-W8.7-P1.70-LS14.4-BR; LCSC Part C134490

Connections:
BRAKE_GND: C1.2, C2.2, D1.2 (A), D7.1 (K), D9.2 (A), U2.3 (GND), U2.5 (ON/OFF), U2.6 (EP); also elsewhere on the board
DISPLAY_5V: D9.1 (K), F1.1, R11.2; also elsewhere on the board
unnamed: D1.1 (K), L1.1, U2.2 (OUTPUT)
unnamed: D7.2 (A), R11.1
unnamed: C2.1, F1.2, L1.2, U2.4 (FEEDBACK)
PWR_MOTOR: C1.1, U2.1 (VIN); also elsewhere on the board

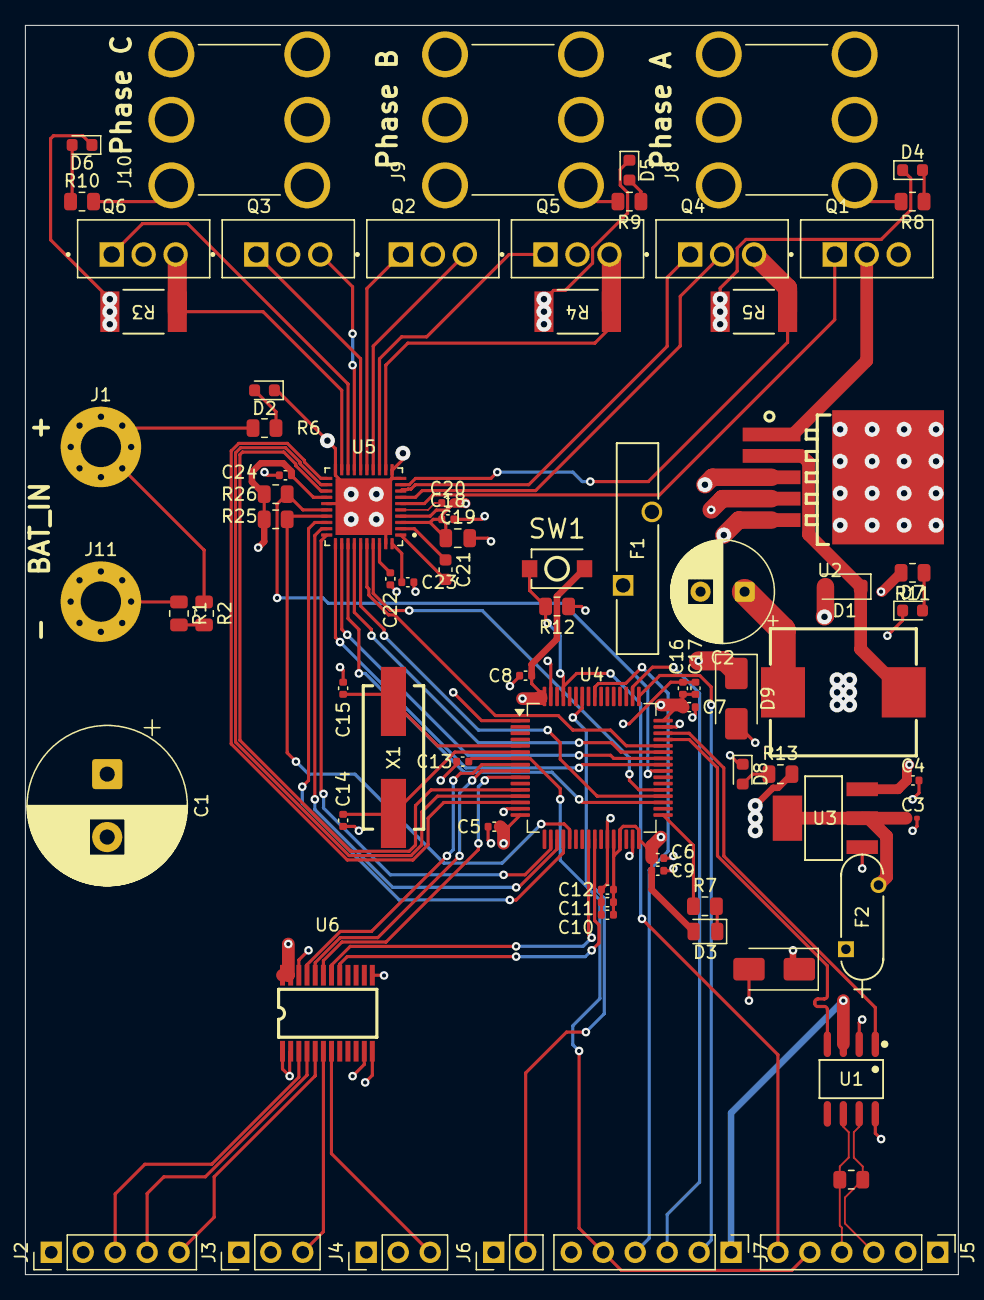
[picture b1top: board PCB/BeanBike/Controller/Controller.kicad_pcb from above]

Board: 4 copper layers, 74.1 x 99.3 mm, 78 parts (0 on the bottom side), 71 nets.
